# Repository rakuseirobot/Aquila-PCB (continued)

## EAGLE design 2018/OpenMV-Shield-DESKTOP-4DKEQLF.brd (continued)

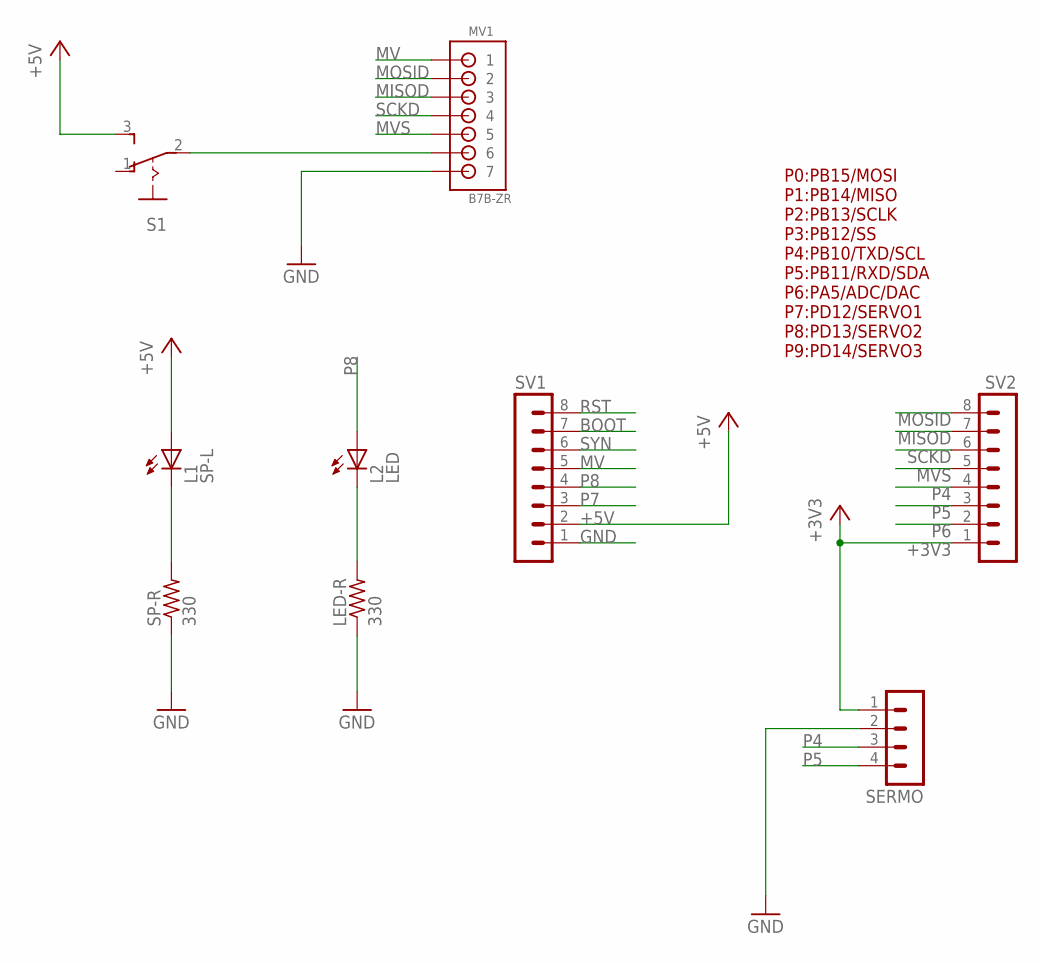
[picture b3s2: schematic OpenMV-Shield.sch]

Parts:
L1: SP-L; CHIPLED_0805
L2: LED; CHIPLED_0805
LED-R: 330; R0805
MV1: B7B-ZR
S1: M251
SERMO: MA04-1
SP-R: 330; R0805
SV1, SV2: MA08-1

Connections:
+3V3: SERMO.1, SV2.1
+5V: L1.A, S1.3 (S), SV1.2; also elsewhere on the board
BOOT: SV1.7
GND: LED-R.1, MV1.7, SERMO.2, SP-R.1, SV1.1
MISOD: MV1.3, SV2.7
MOSID: MV1.2, SV2.8
MV: MV1.1, SV1.5
MVS: MV1.5, SV2.5
unnamed 8: MV1.6, S1.2; also elsewhere on the board
unnamed: L2.C, LED-R.2
unnamed: L1.C, SP-R.2
P4: SERMO.3, SV2.4
P5: SERMO.4, SV2.3
P6: SV2.2
P7: SV1.3
P8: L2.A, SV1.4
RST: SV1.8
SCKD: MV1.4, SV2.6
SYN: SV1.6

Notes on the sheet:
P0:PB15/MOSI P1:PB14/MISO P2:PB13/SCLK P3:PB12/SS P4:PB10/TXD/SCL P5:PB11/RXD/SDA P6:PA5/ADC/DAC P7:PD12/SERVO1 P8:PD13/SERVO2 P9:PD14/SERVO3

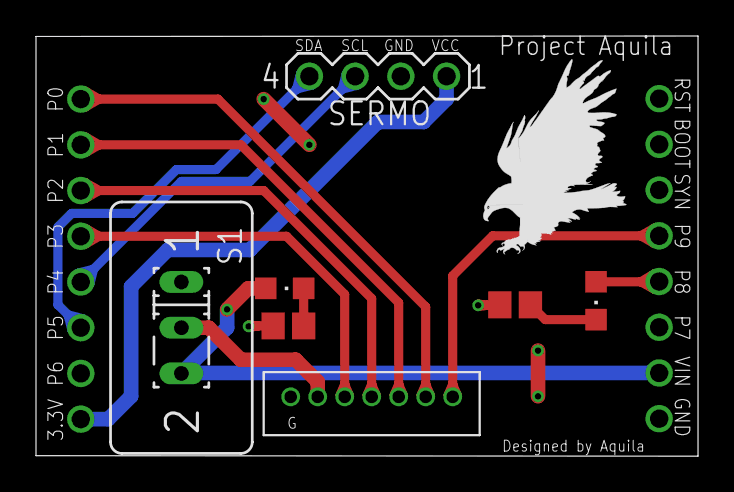
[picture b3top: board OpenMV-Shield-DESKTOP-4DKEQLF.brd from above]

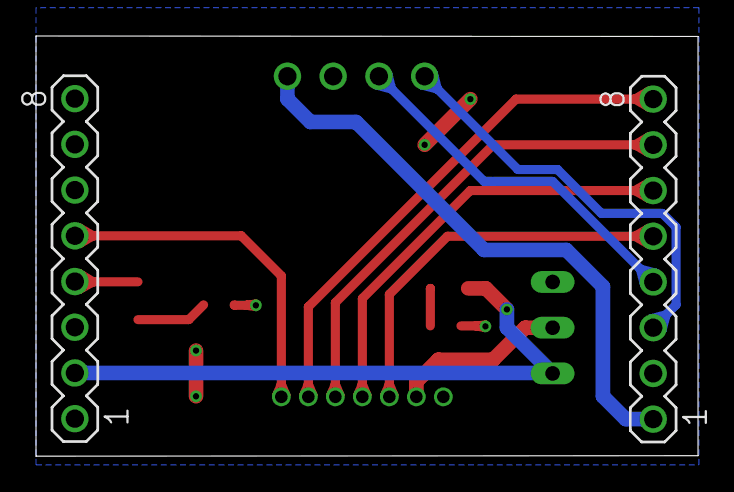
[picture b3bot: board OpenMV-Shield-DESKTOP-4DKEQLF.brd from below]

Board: 2 copper layers, 36.8 x 23.3 mm, 10 parts (2 on the bottom side), 14 nets.

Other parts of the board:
U$1: EAGLE-PLC-8MM
